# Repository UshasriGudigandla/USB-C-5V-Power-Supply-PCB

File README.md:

# USB-C 5V Power Supply PCB

## Project Overview

This project presents the design and PCB implementation of a compact USB-C 5V power supply using KiCad.

The design accepts 5V power through a USB-C connector and provides a protected and filtered 5V output. The PCB includes input protection, decoupling capacitors, transient voltage protection and USB-C CC resistors.

## Project Images

### Schematic

### PCB Layout

### 3D PCB View

## Features

- USB-C 5V power input
- 5V power output interface
- USB-C CC1 and CC2 pull-down resistors
- 500 mA resettable fuse for input protection
- TVS diode for transient voltage protection
- Input/output filtering capacitors
- Two-layer PCB design
- Ground copper zone
- Design Rule Check (DRC) completed
- Gerber and drill fabrication files generated
- 3D PCB model verified in KiCad

## Main Components

| Reference | Component | Function |
|---|---|---|
| J1 | USB-C Receptacle | 5V power input |
| F1 | 500 mA Polyfuse | Overcurrent protection |
| R1 | 5.1 kΩ | USB-C CC1 pull-down |
| R2 | 5.1 kΩ | USB-C CC2 pull-down |
| C1 | 10 µF | Power filtering |
| C2 | 10 µF | Power filtering |
| D1 | SMBJ5.0A TVS | Transient voltage protection |
| J2 | 2-pin connector | 5V output |

## Design Flow

1. Circuit schematic design
2. Component selection
3. PCB footprint assignment
4. PCB placement
5. PCB routing
6. Ground copper zone implementation
7. Design Rule Check (DRC)
8. 3D PCB verification
9. Gerber generation
10. Drill file generation

## PCB Design

The PCB was designed as a two-layer board using KiCad.

The main design considerations were:

- Short power-current paths
- Appropriate component placement
- Ground-plane connectivity
- USB-C connector routing
- Protection component placement
- Manufacturable PCB layout

## Verification

The PCB was checked using KiCad Design Rule Check (DRC).

*The PCB was checked using KiCad Design Rule Check (DRC), and electrical connectivity was verified with 0 unconnected items.*

The completed PCB was also inspected using KiCad 3D Viewer.

## Fabrication Files

The `Gerbers` folder contains the manufacturing files required for PCB fabrication, including:

- Front copper
- Back copper
- Front solder mask
- Back solder mask
- Front silkscreen
- Back silkscreen
- Board Edge Cuts
- Gerber job file
- PTH drill file
- NPTH drill file

## Software Used

- KiCad 10.0
- KiCad Schematic Editor
- KiCad PCB Editor
- KiCad 3D Viewer
- KiCad Gerber Viewer

## Repository Contents

```text
USB-C-5V-Power-Supply-PCB/
│
├── Gerbers/
│   ├── Gerber fabrication files
│   └── Drill files
│
├── project1_USB-C 5v Power Supply PCB.kicad_sch
├── project1_USB-C 5v Power Supply PCB.kicad_pcb
├── project1_USB-C 5v Power Supply PCB.kicad_pro
└── README.md

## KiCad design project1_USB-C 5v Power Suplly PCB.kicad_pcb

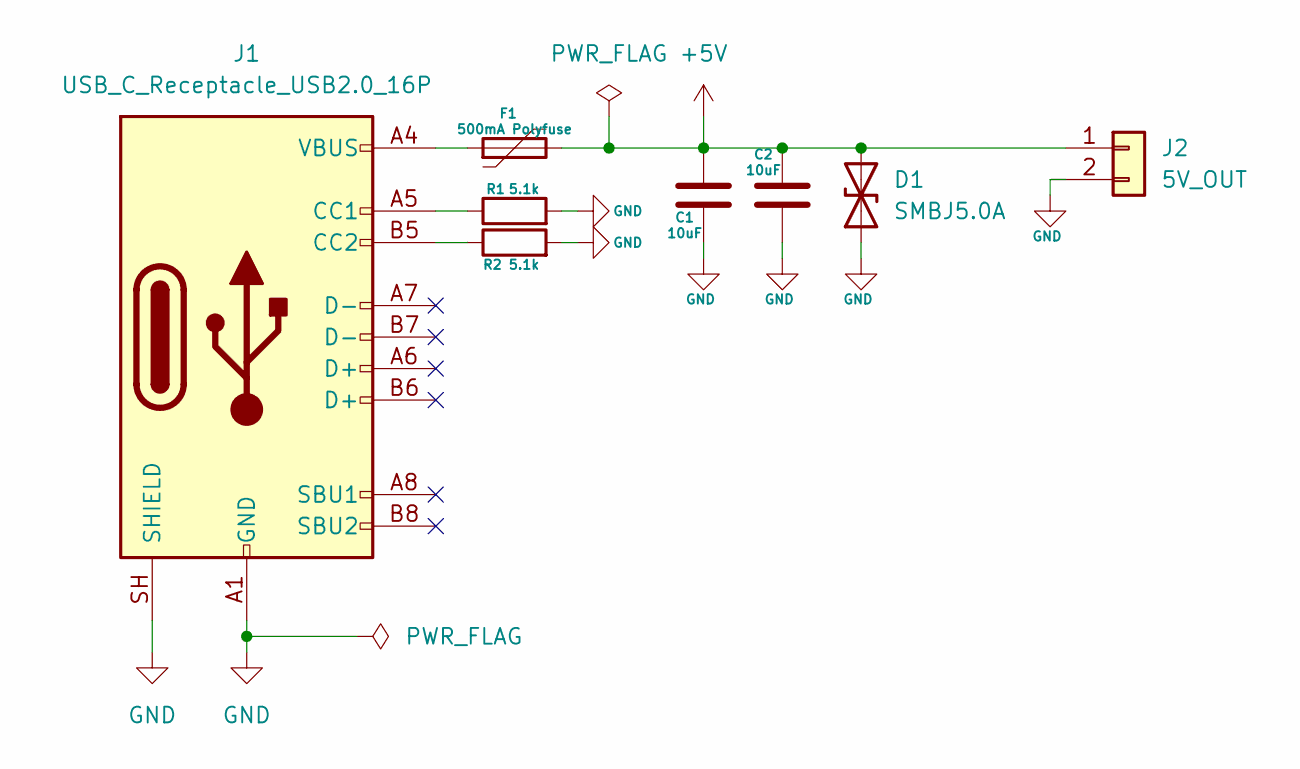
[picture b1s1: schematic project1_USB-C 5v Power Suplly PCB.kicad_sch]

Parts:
C1, C2: 10uF; C_0805_2012Metric
D1: SMBJ5.0A; D_SMB
F1: 500mA Polyfuse; Fuse_1206_3216Metric
J1: USB_C_Receptacle_USB2.0_16P; USB_C_Receptacle_GCT_USB4105-xx-A_16P_TopMnt_Horizontal
J2: 5V_OUT; PinHeader_1x02_P2.54mm_Vertical
R1, R2: 5.1k; R_0805_2012Metric

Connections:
+5V: C1.2, C2.2, D1.2 (A2), F1.2, J2.1
GND: C1.1, C2.1, D1.1 (A1), J1.A1 (GND), J1.A12 (GND), J1.B1 (GND), J1.B12 (GND), J1.SH (SHIELD), J2.2, R1.2, R2.2
unnamed: F1.1, J1.A4 (VBUS), J1.A9 (VBUS), J1.B4 (VBUS), J1.B9 (VBUS)
unnamed: J1.A5 (CC1), R1.1
unnamed: J1.B5 (CC2), R2.1

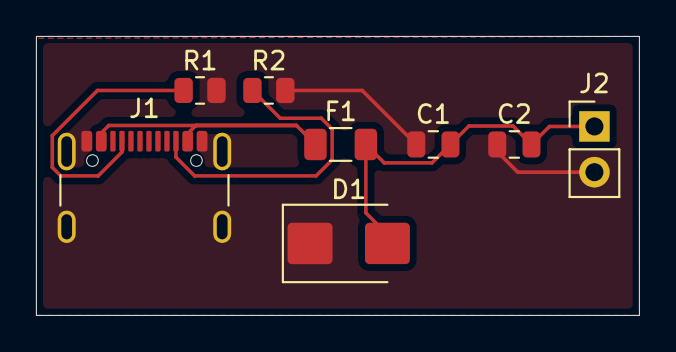
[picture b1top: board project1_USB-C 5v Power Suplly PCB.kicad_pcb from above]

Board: 2 copper layers, 33.5 x 15.5 mm, 8 parts (0 on the bottom side), 5 nets.
